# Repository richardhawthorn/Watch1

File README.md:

### Description

An Arduino multimeter watch

### Multimeter functions

- Displays voltage between 0 and 30v
- Displays current upto 500mA
- Zener clamp and 500mA PTC to protect Arduino

### Features

- ATMEGA328P with Arduino boot-loader
- 3.3V operation with CR2032 battery
- 32.768kHz crystal
- Mini 7 segment display
- 2x side buttons for menu operation
- FTDI programming port
- Low power operation

### Bootloader

You will need to set various fuses when you upload the bootloader, thse can be done with this command

avrdude -b 19200 -c usbtiny -p m328p -v -e -U lfuse:w:0xe2:m -U hfuse:w:0xda:m -U efuse:w:0x07:m

### License

This work is licensed under a Creative Commons Attribution-ShareAlike 4.0 International License.

<br />
Designed by <a xmlns:cc="http://creativecommons.org/ns#" href="http://www.richardhawthorn.com" property="cc:attributionName" rel="cc:attributionURL" target="_blank">Richard Hawthorn</a><br />
<a rel="license" href="http://creativecommons.org/licenses/by-sa/4.0/" target="_blank">View License</a>

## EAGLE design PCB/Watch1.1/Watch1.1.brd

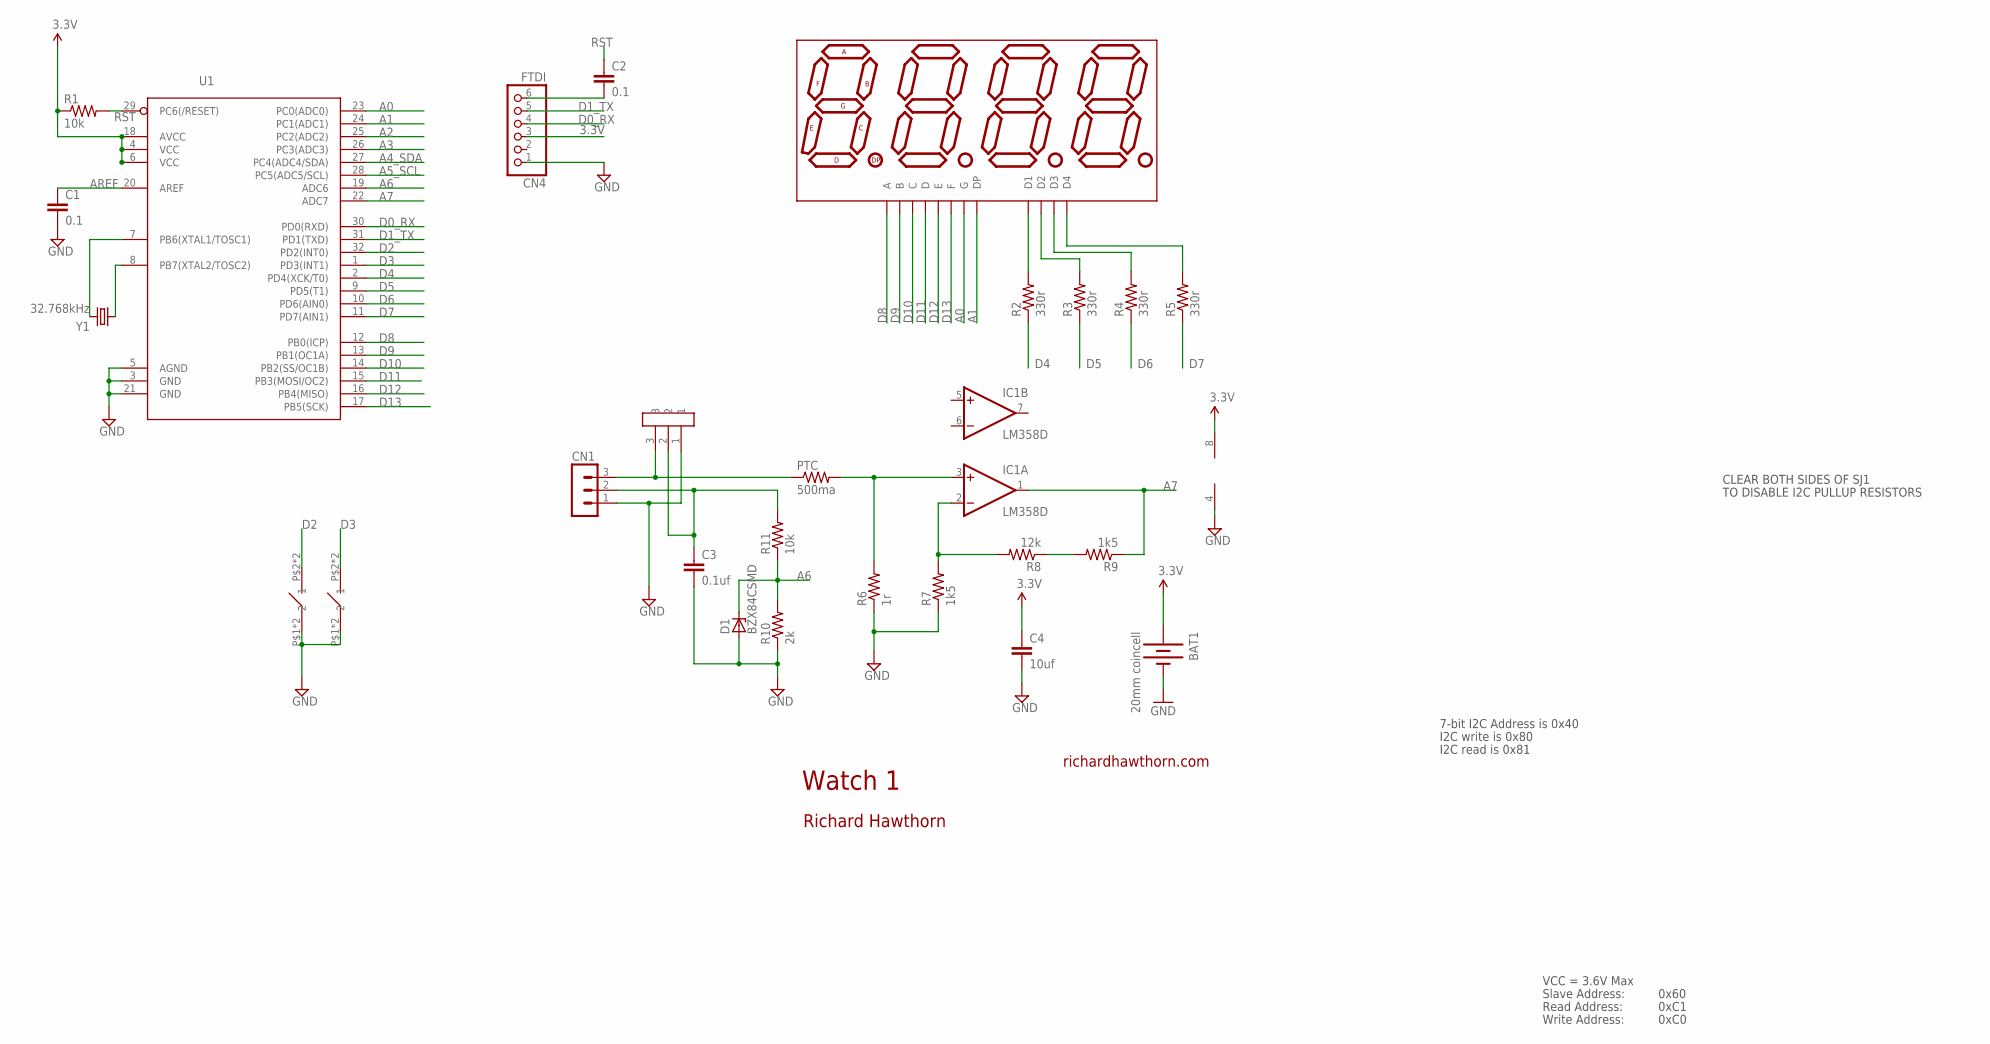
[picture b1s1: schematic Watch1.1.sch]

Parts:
BAT1: 20mm coincell; BATTCON_20MM_4LEGS_OVERPASTE
BTN1, BTN2: TURTLE-3PIN
C1, C2: 0.1; 0603-CAP
C3: 0.1uf; 0603-CAP
C4: 10uf; 0603-CAP
CN1: MA03-1
CN2: 3PIN-HEADER-RA; 3PIN_HEAD_RA
CN4: FTDI; 1X06
D1: BZX84CSMD; TO236
IC1: LM358D; SO08
LED1: HP_DISPLAY; DIL12
PTC: 500ma; R1206
R1: 10k; 0603-RES
R2, R3, R4, R5: 330r; 0805
R6: 1r; 0805
R7, R9: 1k5; 0805
R8: 12k; 0805
R10: 2k; 0805
R11: 10k; 0805
U1: ATMega-328; TQFP32-08
Y1: 32.768kHz; TC26HEZ

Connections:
3.3V: BAT1.1 (+), C4.1, CN4.3, IC1.8 (V+), R1.1, U1.4 (VCC), U1.6 (VCC), U1.18 (AVCC)
A0: LED1.7 (G), U1.23 (PC0(ADC0))
A1: LED1.5 (DP), U1.24 (PC1(ADC1))
A2: U1.25 (PC2(ADC2))
A3: U1.26 (PC3(ADC3))
A4_SDA: U1.27 (PC4(ADC4/SDA))
A5_SCL: U1.28 (PC5(ADC5/SCL))
A6: D1.C, R10.2, R11.1, U1.19 (ADC6)
A7: IC1.1 (OUT), R9.1, U1.22 (ADC7)
AREF: C1.1, U1.20 (AREF)
D0_RX: CN4.4, U1.30 (PD0(RXD))
D1_TX: CN4.5, U1.31 (PD1(TXD))
D2: BTN1.P$2 (2), BTN1.P$4 (2), U1.32 (PD2(INT0))
D3: BTN2.P$2 (2), BTN2.P$4 (2), U1.1 (PD3(INT1))
D4: R2.1, U1.2 (PD4(XCK/T0))
D5: R3.1, U1.9 (PD5(T1))
D6: R4.1, U1.10 (PD6(AIN0))
D7: R5.1, U1.11 (PD7(AIN1))
D8: LED1.12 (A), U1.12 (PB0(ICP))
D9: LED1.11 (B), U1.13 (PB1(OC1A))
D10: LED1.3 (C), U1.14 (PB2(SS/OC1B))
D11: LED1.8 (D), U1.15 (PB3(MOSI/OC2))
D12: LED1.2 (E), U1.16 (PB4(MISO))
D13: LED1.9 (F), U1.17 (PB5(SCK))
GND: BAT1.2 (-), BTN1.P$1 (1), BTN1.P$3 (1), BTN2.P$1 (1), BTN2.P$3 (1), C1.2, C3.2, C4.2, CN1.1, CN2.1, CN4.1, D1.A, IC1.4 (V-), R6.1, R7.1, R10.1, U1.3 (GND), U1.5 (AGND), U1.21 (GND)
unnamed: U1.7 (PB6(XTAL1/TOSC1)), Y1.2
unnamed: LED1.1 (D1), R2.2
unnamed: LED1.10 (D2), R3.2
unnamed: LED1.4 (D3), R4.2
unnamed: LED1.6 (D4), R5.2
unnamed: CN1.3, CN2.3, PTC.1
unnamed: IC1.3 (+IN), PTC.2, R6.2
unnamed: IC1.2 (-IN), R7.2, R8.2
unnamed: R8.1, R9.2
unnamed: U1.8 (PB7(XTAL2/TOSC2)), Y1.1
unnamed: C3.1, CN1.2, CN2.2, R11.2
unnamed: C2.2, CN4.6
RST: C2.1, R1.2, U1.29 (PC6(/RESET))

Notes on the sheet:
Watch 1
richardhawthorn.com
Richard Hawthorn
CLEAR BOTH SIDES OF SJ1
TO DISABLE I2C PULLUP RESISTORS
7-bit I2C Address is 0x40
I2C write is 0x80
I2C read is 0x81
VCC = 3.6V Max
Read Address:
Write Address:
Slave Address:
0x60
0xC1
0xC0

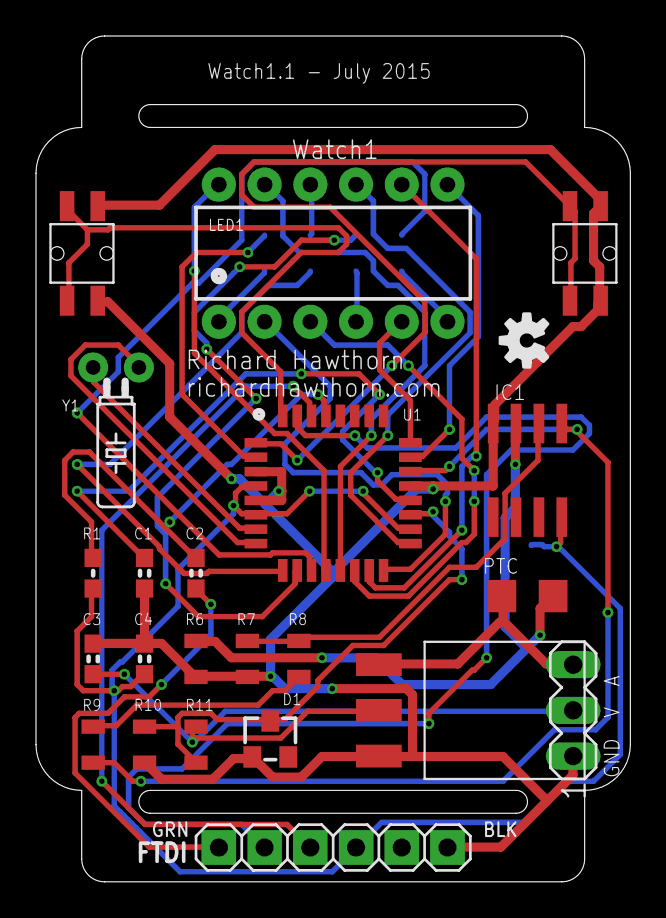
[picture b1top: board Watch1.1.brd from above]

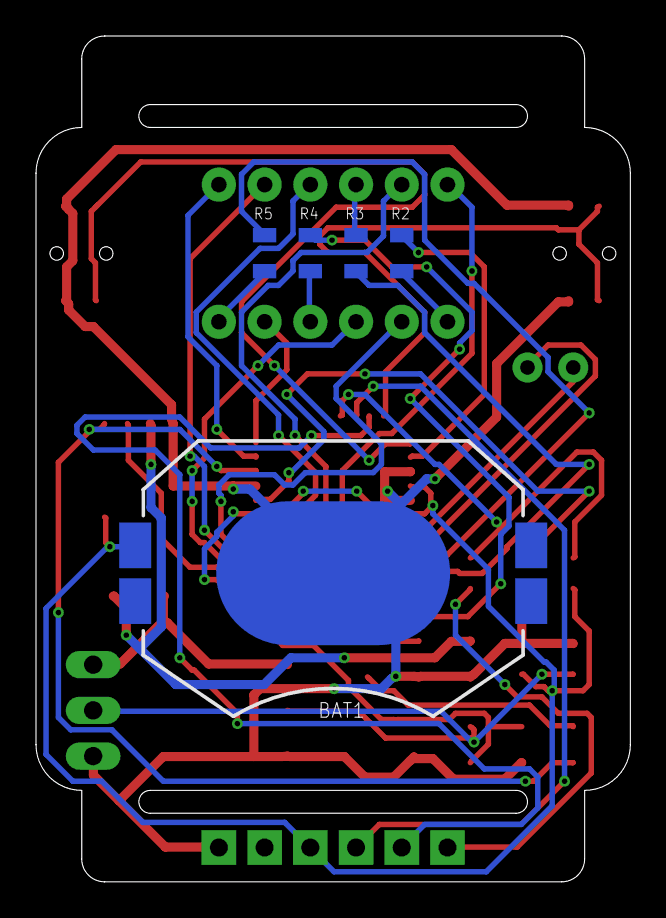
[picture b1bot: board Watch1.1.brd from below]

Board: 2 copper layers, 33.0 x 47.0 mm, 28 parts (5 on the bottom side), 34 nets.

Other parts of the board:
U$3: OSHW-LOGO-S

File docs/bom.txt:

Qty Value          Device                      Package                      Parts          Description                                                                         
1                  MA03-1                      MA03-1                       CN1            PIN HEADER                                                                          
2                  TURTLE-3PIN                 TURTLE-3PIN                  BTN1, BTN2     Buttons                                                                                    
2   0.1            CAP0603-CAP                 0603-CAP                     C1, C2         Capacitor                                                                           
1   0.1uf          CAP0603-CAP                 0603-CAP                     C3             Capacitor                                                                           
1   10k            RESISTOR0603-RES            0603-RES                     R1             Resistor                                                                            
1   10k            RESISTOR0805                0805                         R11            Resistor                                                                            
1   10uf           CAP0603-CAP                 0603-CAP                     C4             Capacitor                                                                           
1   12k            RESISTOR0805                0805                         R8             Resistor                                                                            
2   1k5            RESISTOR0805                0805                         R7, R9         Resistor                                                                            
1   1r             RESISTOR0805                0805                         R6             Resistor                                                                            
1   20mm coincell  BATTERY20MM	               BATTCON_20MM                 BAT1           Battery Holders                                                                     
1   2k             RESISTOR0805                0805                         R10            Resistor                                                                            
1   32.768kHz      CRYSTALTC26H_EZ             TC26HEZ                      Y1             Spark Fun Electronics SKU : COM-00534 
4   330r           RESISTOR0805                0805                         R2, R3, R4, R5 Resistor                                                                            
1   3PIN-HEADER-RA 3PIN-HEADER-RA              3PIN_HEAD_RA                 CN2            3 pin right angle header                                                            
1   500ma          R-US_R1206                  R1206                        PTC            RESISTOR, American symbol                                                           
1   ATMega-328     ATMEGA168/328TQFP32         TQFP32-08                    U1             Atmel 32-pin 8-bit micro, 16k flash.                                                
1   BZX84CSMD      BZX84CSMD                   TO236                        D1             Z DIODE                                                                             
1   FTDI           PINHD-1X6                   1X06                         CN4            PIN HEADER                                                                          
1   HP_DISPLAY     HP_DISPLAY                  DIL12                        LED1           7 Segment LED screen                                                                                    
1   LM358D         LM358D                      SO08                         IC1            OP AMP also LM158; LM258; LM2904

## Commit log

2015-07-04 First version of the watch
2015-07-04 Add readme
2015-07-05 fix diode position
2015-11-05 updated readme and added pcb images
2015-11-05 adjustments
2015-11-05 added bom

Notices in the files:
parts and their libraries:
SparkFun-Aesthetics: Licensing: CC v3.0 Share-Alike You are welcome to use this library for commercial purposes.
